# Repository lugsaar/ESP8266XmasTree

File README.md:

# ESP8266 Xmas Tree

 [![CC BY-NC-SA 4.0][cc-by-nc-sa-shield]][cc-by-nc-sa]

ESP8266 based PCB Xmas tree with WS2812B LEDs as Christmas lights. The Christmas tree can be easily controlled with systems like Tasmota or ESPHome. It is very simple to integrate the Christmas tree into any SmartHome environment. To control the LEDs you can also use the standard development tools for ESP MCUs. To be more flexible, the connection of the MCU and sensor is mounted via female pin header. Components like capacitors are a bit bigger in the footprint to build the Xmas tree without special tools. Only a standard electronic soldering iron and solder is needed. With soldering paste it is a little easier. 

## Building the first batch

<br>

<p align="center">
  <video  src="https://user-images.githubusercontent.com/16343380/206121300-22d0379d-260c-4d33-9b2b-982ff7118add.mp4" width"480"/>
</p>

## Layout

## ToDos

- Fixing EdgeCuts problem to be able to build step file

## License 

This work is licensed under a
[Creative Commons Attribution-NonCommercial-ShareAlike 4.0 International License][cc-by-nc-sa].

[![CC BY-NC-SA 4.0][cc-by-nc-sa-image]][cc-by-nc-sa]

[cc-by-nc-sa]: http://creativecommons.org/licenses/by-nc-sa/4.0/
[cc-by-nc-sa-image]: https://licensebuttons.net/l/by-nc-sa/4.0/88x31.png
[cc-by-nc-sa-shield]: https://img.shields.io/badge/License-CC%20BY--NC--SA%204.0-lightgrey.svg

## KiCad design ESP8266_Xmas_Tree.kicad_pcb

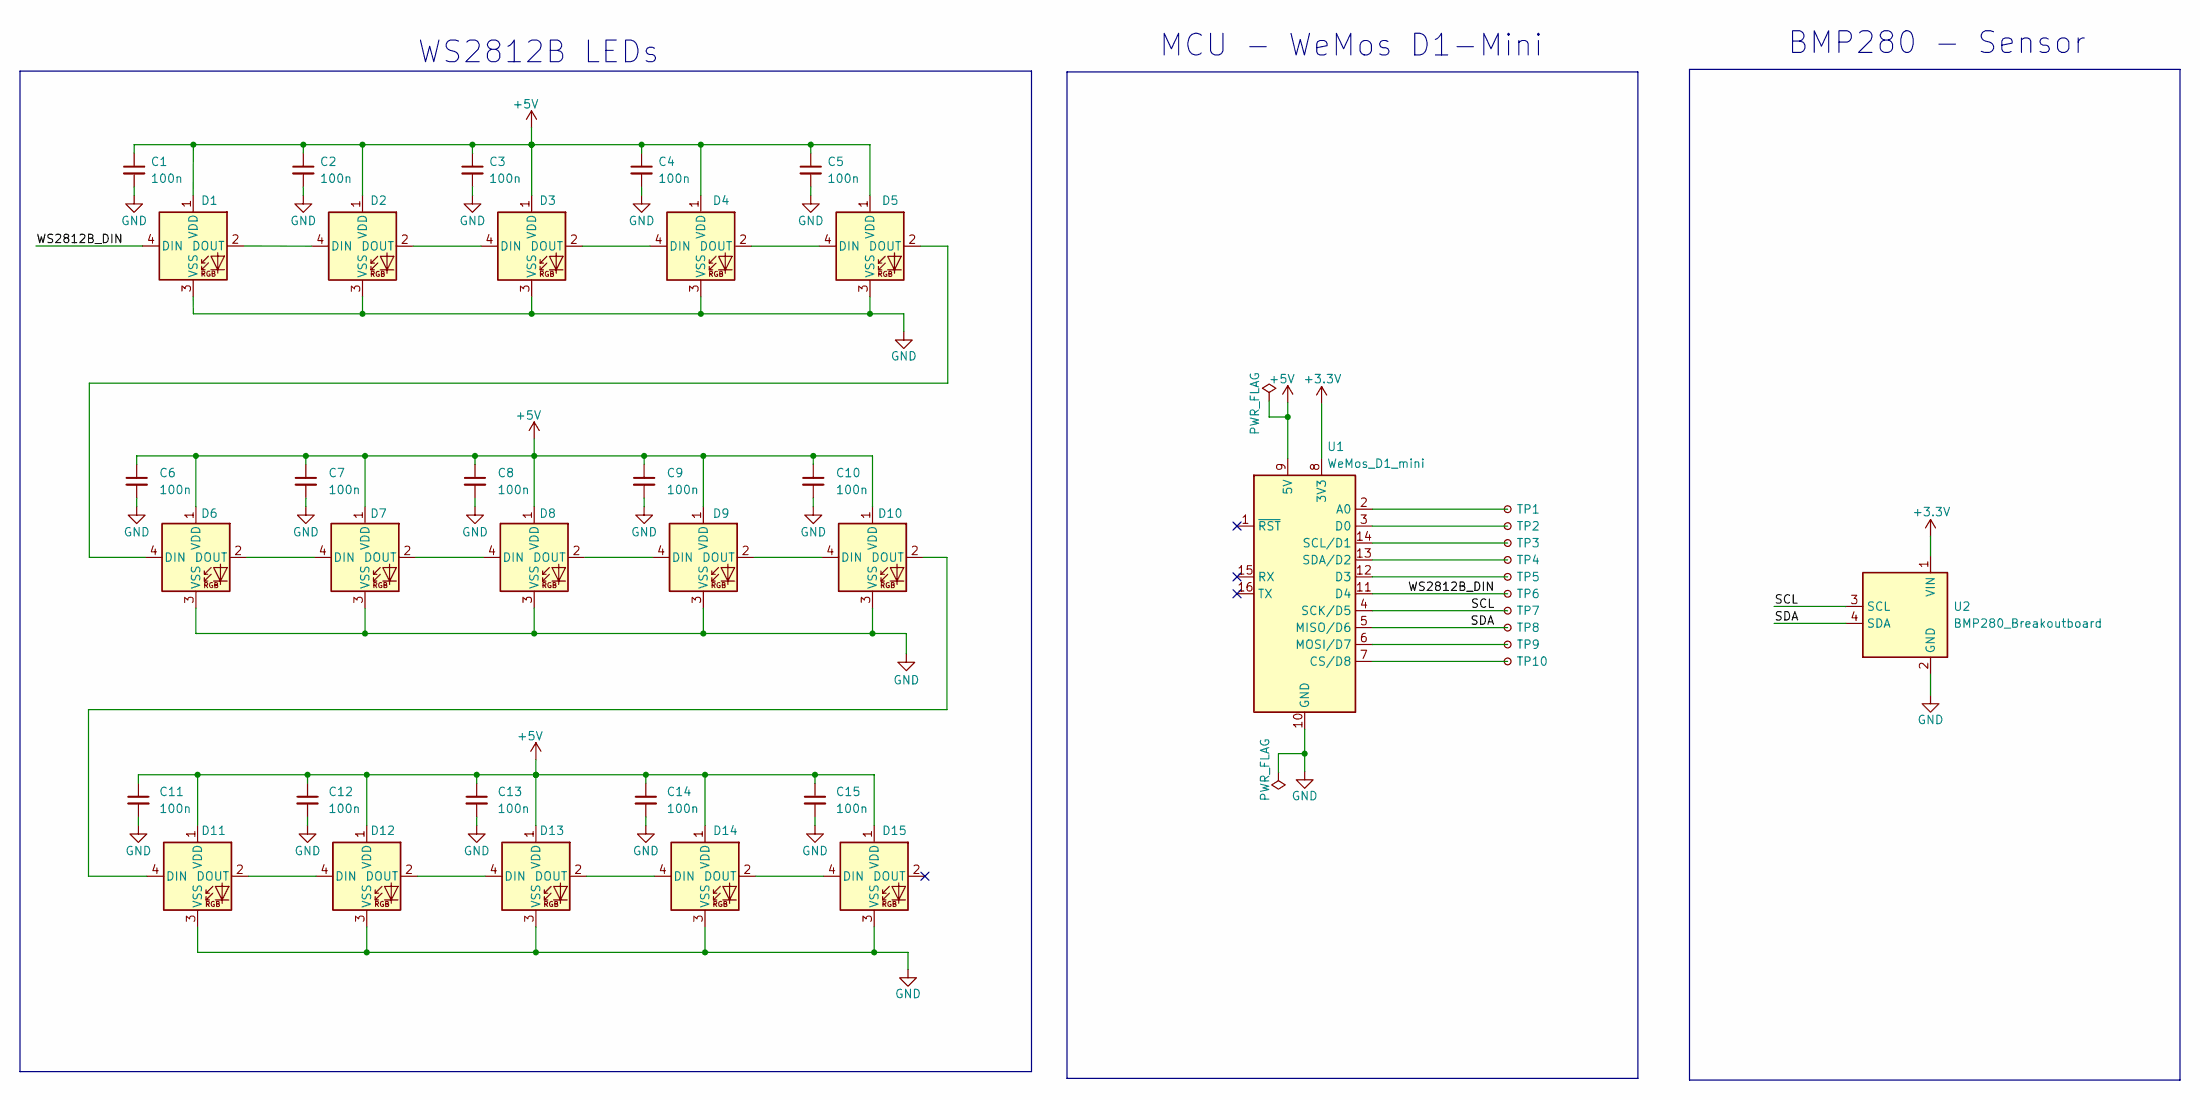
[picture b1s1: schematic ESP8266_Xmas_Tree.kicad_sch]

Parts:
C1, C2, C3, C4, C5, C6, C7, C8, C9, C10, C11, C12, C13, C14, C15: 100n; C_0805_2012Metric_Pad1.18x1.45mm_HandSolder
D1, D2, D3, D4, D5, D6, D7, D8, D9, D10, D11, D12, D13, D14, D15: WS2812B; LED_WS2812B_PLCC4_5.0x5.0mm_P3.2mm
TP1, TP2, TP3, TP4, TP5, TP6, TP7, TP8, TP9, TP10: TestPoint_Small; TestPoint_Pad_D2.0mm
U1: WeMos_D1_mini; WEMOS_D1_mini_light
U2: BMP280_Breakoutboard

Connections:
+3.3V: U1.8 (3V3), U2.1 (VIN)
+5V: C1.1, C2.1, C3.1, C4.1, C5.1, C6.1, C7.1, C8.1, C9.1, C10.1, C11.1, C12.1, C13.1, C14.1, C15.1, D1.1 (VDD), D2.1 (VDD), D3.1 (VDD), D4.1 (VDD), D5.1 (VDD), D6.1 (VDD), D7.1 (VDD), D8.1 (VDD), D9.1 (VDD), D10.1 (VDD), D11.1 (VDD), D12.1 (VDD), D13.1 (VDD), D14.1 (VDD), D15.1 (VDD), U1.9 (5V)
/SCL: TP7.1, U1.4 (SCK/D5), U2.3 (SCL)
/SDA: TP8.1, U1.5 (MISO/D6), U2.4 (SDA)
/WS2812B_DIN: D1.4 (DIN), TP6.1, U1.11 (D4)
GND: C1.2, C2.2, C3.2, C4.2, C5.2, C6.2, C7.2, C8.2, C9.2, C10.2, C11.2, C12.2, C13.2, C14.2, C15.2, D1.3 (VSS), D2.3 (VSS), D3.3 (VSS), D4.3 (VSS), D5.3 (VSS), D6.3 (VSS), D7.3 (VSS), D8.3 (VSS), D9.3 (VSS), D10.3 (VSS), D11.3 (VSS), D12.3 (VSS), D13.3 (VSS), D14.3 (VSS), D15.3 (VSS), U1.10 (GND), U2.2 (GND)
unnamed: D1.2 (DOUT), D2.4 (DIN)
unnamed: D2.2 (DOUT), D3.4 (DIN)
unnamed: D3.2 (DOUT), D4.4 (DIN)
unnamed: D4.2 (DOUT), D5.4 (DIN)
unnamed: D5.2 (DOUT), D6.4 (DIN)
unnamed: D6.2 (DOUT), D7.4 (DIN)
unnamed: D7.2 (DOUT), D8.4 (DIN)
unnamed: D8.2 (DOUT), D9.4 (DIN)
unnamed: D10.2 (DOUT), D11.4 (DIN)
unnamed: D9.2 (DOUT), D10.4 (DIN)
unnamed: D11.2 (DOUT), D12.4 (DIN)
unnamed: D12.2 (DOUT), D13.4 (DIN)
unnamed: D13.2 (DOUT), D14.4 (DIN)
unnamed: D14.2 (DOUT), D15.4 (DIN)
unnamed: TP1.1, U1.2 (A0)
unnamed: TP2.1, U1.3 (D0)
unnamed: TP3.1, U1.14 (SCL/D1)
unnamed: TP4.1, U1.13 (SDA/D2)
unnamed: TP5.1, U1.12 (D3)
unnamed: TP9.1, U1.6 (MOSI/D7)
unnamed: TP10.1, U1.7 (CS/D8)

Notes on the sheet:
BMP280 - Sensor
WS2812B LEDs
MCU - WeMos D1-Mini

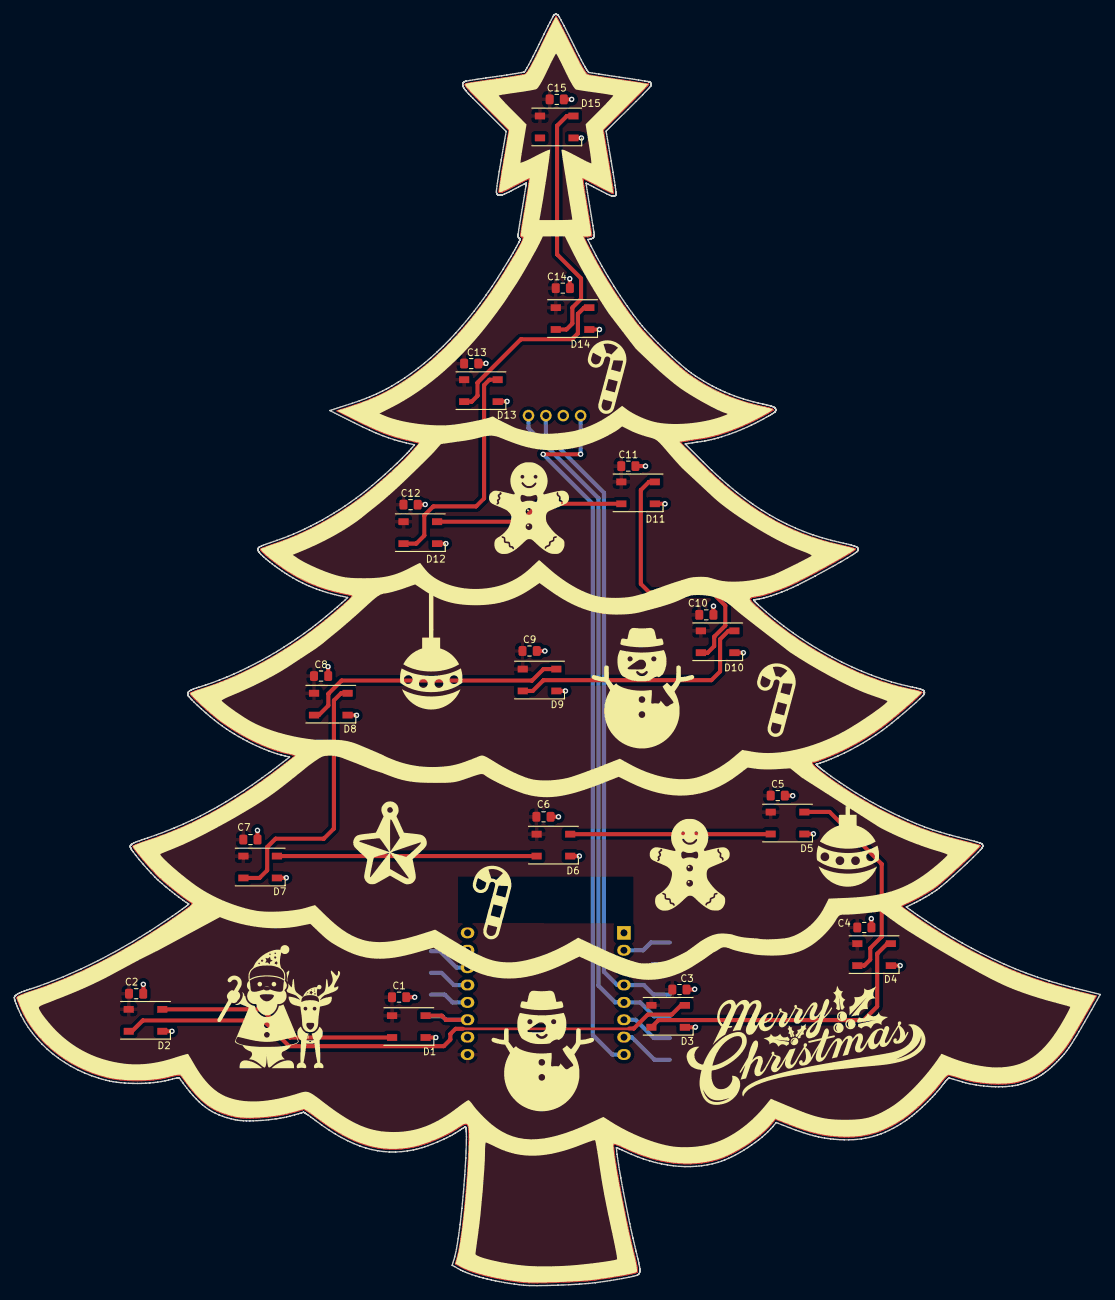
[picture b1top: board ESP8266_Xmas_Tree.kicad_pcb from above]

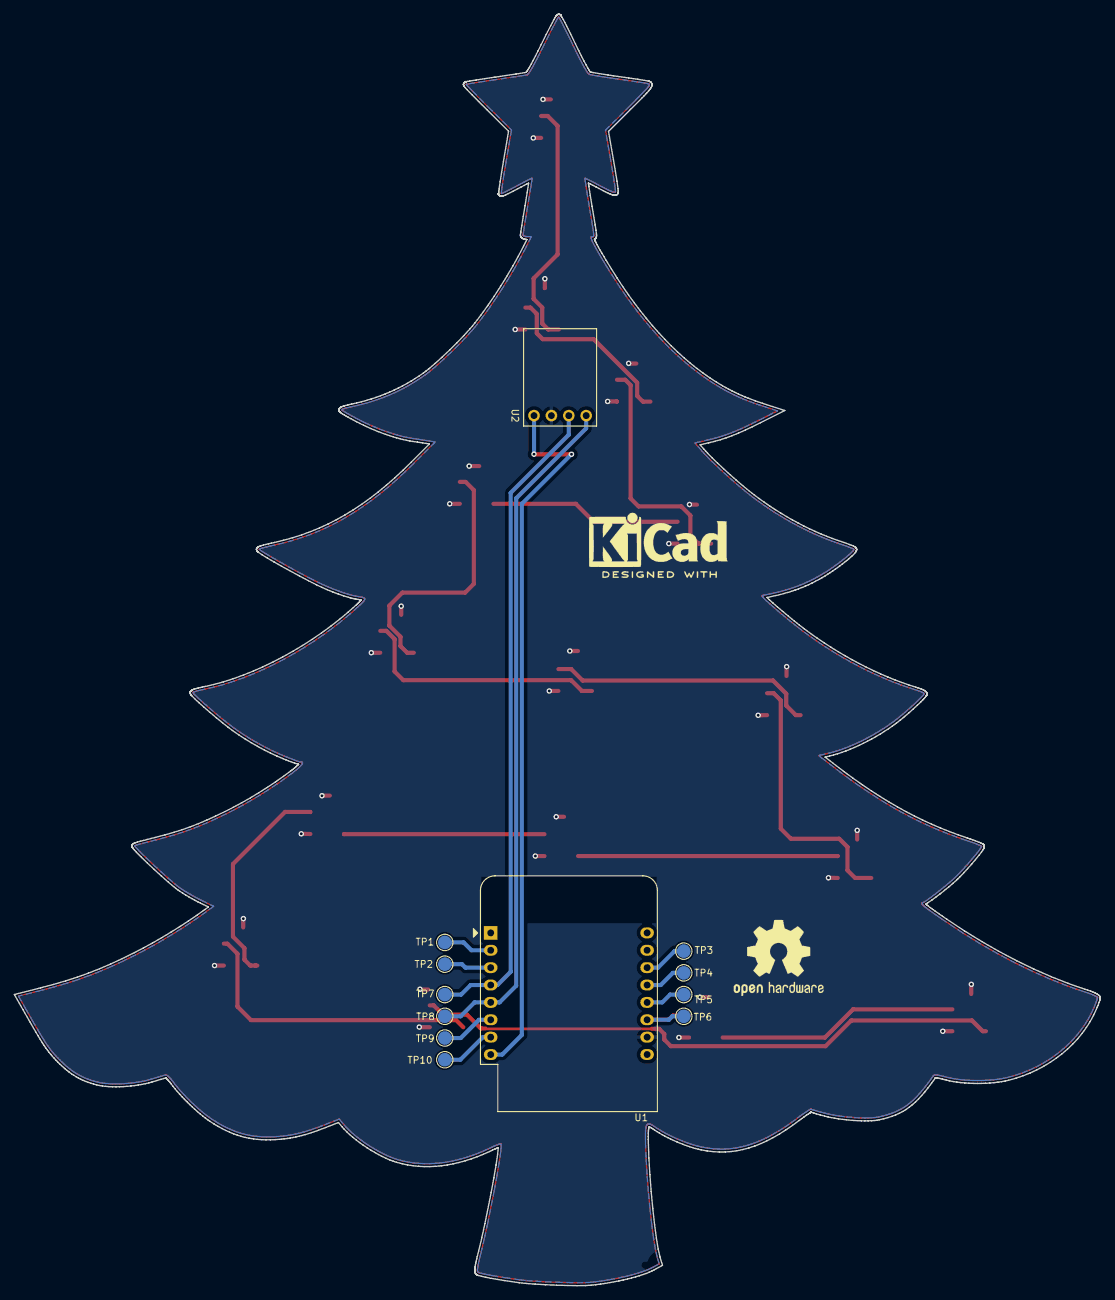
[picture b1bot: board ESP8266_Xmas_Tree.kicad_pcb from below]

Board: 2 copper layers, 158.7 x 185.8 mm, 42 parts (12 on the bottom side), 27 nets.

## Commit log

2022-10-25 first init
2022-10-26 adding some nice graphics like gingerbreak man and snowflakes to silkscreen
2022-10-26 adding d1 mini step model to pcb
2022-10-27 adding caps for WS2812B LEDs
2022-10-28 adding 3V3 and GND to MCU
2022-10-30 adding Edge Cuts, Silkscreen an filled zones from SVG files
2022-10-30 adding Xmas balls, canes and santa claus to PCB in silkscreen
2022-11-02 Fix the naming error of the capacitors and change the supply voltage from 3V3 to 5V of the LEDs.
2022-11-03 adding BMP280 Breakoutboard Lib and footprint to PCB
2022-11-04 first routing
2022-11-05 adding README file
2022-11-06 Adding some description to README file.
2022-11-06 ignoring Gerber files in repo
2022-11-20 adding gitattributes files
2022-11-23 XmasTree code for ESP D1 mini added
2022-11-23 XmasTreeStand added, brightness reduced
2022-11-24 start blinking with movie 2
2022-12-01 Port firmware from Arduino IDE to platformio development environment
2022-12-01 Adding LICENSE file and section in README file
2022-12-02 Xmastre stand update
2022-12-06 adding pic of first built
2022-12-07 adding Video to README file
2022-12-07 beautifing readme.md
2022-12-10 XmastreeStand extended for big usb connectors
